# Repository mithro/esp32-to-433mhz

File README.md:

# esp32-to-433mhz

> [!CAUTION]
> **AI in use, use at own risk.**

A small carrier board that turns an **ESP32-C3 SuperMini** and a cheap
**433 MHz radio board** into one 29&nbsp;x&nbsp;38 mm unit. It takes any of three
common 2x4-header radios in the same socket:

* the blue **Ebyte E07-M1101D** (CC1101, SMA jack),
* the green **D-Sun CC1101** board (same signals, different header order),
* the blue **SX1278 LoRa 433MHz v4.0** breakout (Ai-Thinker Ra-02, IPEX
  antenna).

Same ESP32 pins for every radio, one firmware pin map per board, and every
track on one copper layer so it can even be etched at home.

| With the E07-M1101D (CC1101) | With the Ra-02 breakout (SX1278) |
| --- | --- |
|  |  |

The KiCad 9 project is `hardware/esp32c3-radio-adapter`. Ready-to-upload
Gerber packages are attached to the
[latest release](https://github.com/mithro/esp32-to-433mhz/releases/latest).

Contents:

* [What you need](#what-you-need)
* [Getting the board made](#getting-the-board-made)
* [Assembling it](#assembling-it)
* [Pin map for firmware](#pin-map-for-firmware)
* [Jumper-wire version (no adapter needed)](#jumper-wire-version-no-adapter-needed)
* [Further reading](#further-reading)

## What you need

Everything is a stock AliExpress / eBay / Amazon part costing a few
dollars. The "Buy" links are AliExpress searches for the listing names;
the "Details" links go to that board's page in this repository, with its
dimensions, pinout and sources.

### Boards

| Board | Buy | How to recognise it | Details |
| --- | --- | --- | --- |
| **ESP32-C3 SuperMini** | [ESP32-C3 SuperMini](https://www.aliexpress.com/w/wholesale-esp32-c3-supermini.html) | 18&nbsp;x&nbsp;22.5 mm, USB-C, 8 castellated pins per side, ceramic antenna at the far end from the USB-C. Usually ships with two 1x8 pin headers. | [dimensions and pinout](hardware/parts/esp32-c3-supermini/) |
| **One radio board**, any of: | | | |
| Ebyte E07-M1101D-SMA (CC1101) | [E07-M1101D](https://www.aliexpress.com/w/wholesale-e07-m1101d.html), also sold as "TENSTAR CC1101 433MHz wireless module" | Blue, 15&nbsp;x&nbsp;30 mm, 2x4 header at one end, SMA jack at the other, PCB marked "E07-M1101D V2.0". Take the -SMA, not the -TH spring-antenna variant that search leads with. Needs a 433 MHz SMA antenna (often included). | [Ebyte product page](https://www.cdebyte.com/products/E07-M1101D-SMA), [part page](hardware/parts/cc1101-e07-m1101d/) |
| D-Sun CC1101 (green) | [CC1101 433MHz module](https://www.aliexpress.com/w/wholesale-cc1101-433mhz-module.html), pick the green one | Green, 14.4&nbsp;x&nbsp;30 mm, silk "433MHz D-Sun CC1101", 2x4 header, SMA jack. Needs a 433 MHz SMA antenna. | [part page](hardware/parts/cc1101-dsun/) |
| SX1278 Ra-02 breakout | [SX1278 LoRa 433MHz Ra-02](https://www.aliexpress.com/w/wholesale-sx1278-lora-433mhz-ra-02.html) | Blue 17.5&nbsp;x&nbsp;22.5 mm carrier with the Ai-Thinker Ra-02 can on top, 2x4 header underneath, silk "SX1278 LoRa 433MHz v4.0". Needs a [U.FL (IPEX) to SMA pigtail](https://www.aliexpress.com/w/wholesale-ipex-to-sma-pigtail.html) plus a 433 MHz SMA antenna. | [Ai-Thinker Ra-02 page](https://docs.ai-thinker.com/en/Ra-02/index.html), [part page](hardware/parts/sx1278-ra02-breakout/) |

Get a [433 MHz SMA antenna](https://www.aliexpress.com/w/wholesale-433mhz-sma-antenna.html),
not the 868/915 MHz one many listings bundle with the same radio.

### Headers and small parts

| Ref | Part | Qty | Notes |
| --- | --- | --- | --- |
| J1, J2 | 1x8 male pin header, 2.54 mm | 2 | For the SuperMini; usually in the bag with it. Or solder the SuperMini flat by its castellations and skip these. |
| J3 | 2x4 male pin header, 2.54 mm | 1 | The radio board's own header solders straight into the adapter. Fit a 2x4 female header instead if you want the radio removable. |
| [J4](docs/design-notes.md#expansion-header-j4) | 1x7 male pin header, 2.54 mm | 1 | Expansion header: 3V3 and the spare GPIOs. Optional. |
| [J5](docs/design-notes.md#the-dio2-fly-wire-header) | 1x2 male pin header, 2.54 mm | 1 | DIO2 fly-wire header. Only needed for raw OOK on the SX1278. |
| [JP1](docs/design-notes.md#radio-type-strap-jp1-r1) | 1x2 male pin header + jumper cap, 2.54 mm | 1 | Radio-type strap. Jumper fitted for the Ra-02, open for a CC1101. |
| R1 | 0805 0 ohm resistor | 0 or 1 | Permanent alternative to the JP1 jumper (Ra-02 only). |
| R2, R3, R4 | 0805 4.7 kOhm resistors | 0 | Do-not-populate pull-ups on the boot straps: GPIO8 and GPIO2 (on J4) and GPIO9 (unused). Only if something you add holds one of them low at boot. |
| | M2 screws or standoffs | 4 | The corner holes are 2.2 mm. |
| | Thin insulated wire, 30 to 50 mm | 1 | The DIO2 fly wire (Ra-02 only): a strand of wire-wrap or enamelled wire. |

A strip of 40-pin "breakaway" male header covers J1, J2, J4, J5 and JP1.

## Getting the board made

1. Download `esp32c3-radio-adapter-<version>-jlcpcb.zip` or
   `...-nextpcb.zip` from the
   [latest release](https://github.com/mithro/esp32-to-433mhz/releases/latest).
   Each zip is a complete Gerber + drill package for that fab, with a
   `README.txt` of the ordering options.
2. Upload the zip to [JLCPCB](https://jlcpcb.com) or
   [NextPCB](https://www.nextpcb.com) as a new PCB order.
3. Order with these options (all fab defaults, no special processes):

| Option | Value |
| --- | --- |
| Size | 29.0&nbsp;x&nbsp;38.0 mm |
| Layers | 2 |
| Thickness | 1.6 mm FR-4 |
| Copper | 1 oz |
| Finish | ENIG preferred, HASL fine |
| Solder mask / silk | any colour, silkscreen both sides |
| Castellated holes | not needed |

The packages are rebuilt by CI on every push to `main` and carry the
`git describe` version in their name; the same string is printed in the
board's title block.

**Etching it yourself.** Every track is on the bottom copper; the top has
only pads and a ground pour. So the bottom layer alone works as a
single-sided board, with two limits: the SuperMini must go on with pin
headers (laid flat it would sit on the copper side, where its pin rows
come out mirrored), and R1 sits on the copper side. Use the `.GBL`,
`.GBO` and `.DRL` files from the package.

## Assembling it

1. **Radio-type strap first.** For the Ra-02 breakout, fit JP1 and put a
   jumper on it (or solder a 0 ohm resistor in R1 on the bottom). For
   either CC1101 board, leave JP1 empty or open.
2. **SuperMini.** It lies on its side along the left edge, USB-C hanging
   off the board; the silk shows the outline and pin names. Either solder
   its two 1x8 headers through the 1.0 mm holes (long pins down through
   the adapter, the plastic body between the two boards), or lay it flat
   on the top side and solder the castellations to the extended pads.
3. **J4, J5.** Optional; solder them from the top so the pins stand up.
   The silk under J4 names the pins the way the SuperMini does; J5's pins
   are "21" and "20 DIO2".
4. **Radio board.** It plugs in component side up, hanging off the bottom
   edge with its antenna connector pointing away from the adapter. Pin 1
   (GND) is the square pad at the right of the outer row. Solder its
   header pins into the 2x4 holes, or into a female socket fitted there.
5. **DIO2 fly wire (Ra-02, raw OOK only).** Run a wire from the
   breakout's DIO2 land to J5 pin 2 (GPIO20). DIO2 is not on the 2x4
   header: it is the Ra-02 module's pin 7, whose land sticks 0.8 mm out
   past the module's edge on the right-hand side, about 9 mm down from the
   header edge. The pinout diagram below marks it, and
   [Adding the DIO2 wire](hardware/parts/sx1278-ra02-breakout/dio2-wire.md)
   shows the radio end and how to check it landed.
6. **Antenna.** Screw it on the E07 or D-Sun's SMA jack; for the Ra-02,
   clip the pigtail's U.FL plug onto the module and screw the antenna on
   the pigtail. The DIO2 wire and the pigtail both want strain relief:
   a dab of hot glue over the wire's solder joint is enough.

| Top | Bottom (all the tracks) |
| --- | --- |
|  |  |

The silkscreen outlines the two mechanical keep-outs, the footprints of the
SuperMini and of the plugged-in radio board. J5 sits in the band between
them and is the only thing that fits there.

## Pin map for firmware

The socket's eight positions go to fixed GPIOs. Which signal each carries
depends on the radio, so firmware needs one pin map per board:

| Socket position | ESP32-C3 GPIO | E07-M1101D (blue CC1101) | D-Sun (green CC1101) | Ra-02 breakout (SX1278) |
| --- | --- | --- | --- | --- |
| 1 | GND | GND | GND | GND |
| 2 | 3V3 | VCC | VCC | 3V3 |
| 3 | GPIO10 | GDO0 (radio out) | MOSI | RST (radio in) |
| 4 | GPIO1 | CSN | SCK | NSS |
| 5 | GPIO3 | SCK | MISO (radio out) | SCK |
| 6 | GPIO4 | MOSI | GDO2 (radio out) | MOSI |
| 7 | GPIO7 | MISO (radio out) | GDO0 (radio out) | MISO (radio out) |
| 8 | GPIO6 | GDO2 (radio out) | CSN | DIO0 (radio out) |
| J5 pin 2 | GPIO20 | | | DIO2/DATA (fly wire) |
| JP1 / R1 | GPIO5 | open | open | strapped to GND |

The same maps, signal first:

| Signal | E07-M1101D | D-Sun | Ra-02 |
| --- | --- | --- | --- |
| MOSI | GPIO4 | GPIO10 | GPIO4 |
| MISO | GPIO7 | GPIO3 | GPIO7 |
| SCK | GPIO3 | GPIO1 | GPIO3 |
| CSN / NSS | GPIO1 | GPIO6 | GPIO1 |
| GDO0 / DIO0 | GPIO10 | GPIO7 | GPIO6 |
| GDO2 | GPIO6 | GPIO4 | |
| RST | | | GPIO10 |
| DIO2/DATA | | | GPIO20 |

**Telling the boards apart.** GPIO5 is the radio-type strap. Read it with
the internal pull-up enabled: low means the Ra-02 (jumper fitted), high
means a CC1101 board. The three-state read that also covers the SX1278
module adapter is in the
[design notes](docs/design-notes.md#radio-type-strap-jp1-r1). The two
CC1101 boards are told apart without driving anything: an unconfigured CC1101 clocks about 135 kHz out of GDO0, so
whichever of GPIO10 (blue board) and GPIO7 (green board) is toggling at
power-up names the board. In the jumper-wire build the strap goes to GPIO0
instead of GND, so drive GPIO0 low as an output before reading GPIO5.

**Why DIO2 matters on the SX1278.** In its continuous mode the raw
demodulated bitstream is available only on the DIO2/DATA pin. Packet mode
carries only what the packet handler can frame, which suits Fineoffset
weather stations but not the OOK remotes this node exists to hear and key.
The Ra-02 breakout leaves DIO2 unconnected, hence the fly wire to GPIO20.

**Never put a radio pin on GPIO2, GPIO8 or GPIO9.** They are ESP32-C3 boot
straps; a radio pin's capacitance makes the strap rise too slowly at reset
and the chip drops into USB download mode instead of running. This was
measured on the bench and later confirmed over JTAG -- on an affected board
the GPIO_STRAP_REG latch reads the download pattern even though the live
GPIO9 reads high -- and is not fixable in software, which is why the socket
uses GPIO1 rather than GPIO9.

## Jumper-wire version (no adapter needed)

The same hook-up with Dupont jumper wires, so the firmware pin map is
identical and you can test everything before ordering boards. Plug the
female-to-female wires onto the SuperMini's headers and the radio board's
2x4 header. Both boards are drawn from the back, pins towards you.

| Wire | SuperMini pin | E07-M1101D | D-Sun | Ra-02 |
| --- | --- | --- | --- | --- |
| brown | G | GND | GND | GND |
| red | 3V3 | VCC | VCC | 3V3 |
| grey | GPIO10 | GDO0 | MOSI | RST |
| purple | GPIO1 | CSN | SCK | NSS |
| blue | GPIO3 | SCK | MISO | SCK |
| white | GPIO4 | MOSI | GDO2 | MOSI |
| green | GPIO7 | MISO | GDO0 | MISO |
| yellow | GPIO6 | GDO2 | CSN | DIO0 |
| orange | GPIO5 | not fitted | not fitted | to the SuperMini's GPIO0 (radio-type strap) |
| black | GPIO20 | | | DIO2, soldered to the module's pin-7 land |

The Ra-02's orange strap wire goes to GPIO0 rather than GND because the
SuperMini's only GND pin is taken by the brown wire; the firmware drives
GPIO0 low while it reads the strap. The black DIO2 wire has no header pin
at the radio end: solder it to the module's pin-7 castellation or the land
just outside it, on the face away from the header pins. The header
pinouts, with the DIO2 land marked on both faces:

## Printing a case

A two-part case that fits the adapter with either radio is in
`hardware/case/` as STL files. Every
[release](https://github.com/mithro/esp32-to-433mhz/releases/latest)
carries it as `esp32c3-radio-adapter-case-<version>.zip`, plus the two
`.stl` files loose for dropping straight into a slicer. The zip holds the
STL files in print orientation, the case's STEP models, and a README.txt
with the parts' sizes, home FDM print settings and how to order them from
JLCPCB's 3D-printing service.
In the pictures and the notes below, the **front** is the antenna end,
the **back** the SuperMini end with the pry notch on the seam, and the
**left** wall the one with the USB-C window. The top half is the darker
shade.

Closed, with the E07-M1101D inside (its SMA jack through the front wall):

Open, the adapter pressed onto the pegs in the bottom half, with the Ra-02
breakout and its U.FL-to-SMA pigtail in the socket (the drawn pigtail runs
straight to the bulkhead; a real one is longer, with the excess lying
beside the breakout):

The halves on their own, and the slotted top:

| Bottom half: pegs, lip and the four snap tabs | Top half from below: bosses, grooved skirt, USB-C window, antenna hole | The slotted top half closed over the E07 |
| --- | --- | --- |
|  |  |  |

The same views with the other radio (the Ra-02 closed, the E07-M1101D
open) and the exploded views are in
[3D models and case design](docs/3d-models.md#the-printed-case).

* Two halves that snap together: `esp32c3-radio-adapter-case-bottom.stl`
  and `esp32c3-radio-adapter-case-top.stl`, each printed open side up. No
  supports, no screws; 2.2 mm walls; 36.2&nbsp;x&nbsp;66.7&nbsp;x&nbsp;16.7 mm
  outside. Trim every pin under the board to about 1 mm first: the floor
  counts on it.
* The board presses onto four 2.15 mm pegs in the bottom half (they fit
  the 2.2 mm M2 corner holes), and bosses in the top half hold it there
  once the case is shut. The SuperMini can be on its headers or soldered
  flat by its castellations.
* The seam runs through the connectors: the antenna hole and the USB-C
  window are half in each half, so the connectors lie in the bottom half's
  cut-outs and the top closes over them. One 6.6 mm hole in the front wall
  serves both radios: the E07-M1101D's SMA jack pokes through it, and the
  Ra-02's U.FL-to-SMA pigtail bulkhead is clamped in it by its nut, with
  the spare cable stowed beside the breakout.
* Four snap tabs on the bottom half click into grooves in the top half's
  skirt; the notch at the seam on the back takes a fingernail to open it.
  It is not water-tight and does not try to be.
* `esp32c3-radio-adapter-case-top-slot.stl` is the same top half with a
  slot over the spare-GPIO header J4, for jumper wires out of the closed
  case; print it instead of the plain top if you want that.
* The package's README.txt has the print settings, what to inspect (the
  0.8 mm snap tabs, the peg fit, which depends on the printer's
  calibration) and the material to pick at a service.

The case is generated from the same dimensions as the boards by
`scripts/build_case.py`; see [3D models and case design](docs/3d-models.md#the-printed-case).
Dimensioned drawings of both halves, with a checklist of caliper
measurements for a printed part, are in [Case drawings](docs/case-drawings.md).

## Further reading

* [Design notes](docs/design-notes.md): why the GPIOs are what they are,
  how everything routes on one layer, the expansion header J4, the DIO2
  header J5, the mechanical keep-outs and the radio-type strap.
* [Component boards](hardware/parts/): a page per board -- the SuperMini
  and each radio -- with its dimensions, pinout, where to buy it and the
  KiCad reproduction its footprints were checked against.
* [3D models and case design](docs/3d-models.md): STEP/GLB assemblies on
  every release, the dimensions a case needs, and the printed case.
* [SX1278 castellated module adapter](docs/sx1278-module-adapter.md): a
  second, two-layer carrier for the solder-down 16-pin SX1278 module,
  `hardware/esp32c3-sx1278-adapter`.
* [Development](docs/development.md): regenerating the KiCad projects
  from the scripts, running ERC/DRC, and how CI builds the release
  packages.

Not part of this repository, but worth a look before writing firmware from
scratch:
[OpenMQTTGateway's RF gateway](https://docs.openmqttgateway.com/use/rf.html#what-is-an-rf-gateway)
is ESP32 firmware that bridges 433&nbsp;MHz to MQTT and already supports both
radio families this adapter takes: CC1101 boards and SX127x modules. It
offers four receiver flavours -- RCSwitch, Pilight and RF2 receive and
transmit, RTL_433 receives only but knows the most devices. Its documented
ESP32 + CC1101 builds are named as whole boards (Heltec WiFi LoRa 32,
LilyGo LoRa 32, ESP32 DOIT DevKit, Ai-Thinker R01) rather than as a pin
map, so this adapter's GPIOs would have to be mapped onto it, and the
SX1278's DIO2 fly wire has no obvious counterpart there. **Nothing here has
been tried against it yet** -- this is a lead to follow, not a tested route.

## Licence

Apache License 2.0, see `LICENSE`.

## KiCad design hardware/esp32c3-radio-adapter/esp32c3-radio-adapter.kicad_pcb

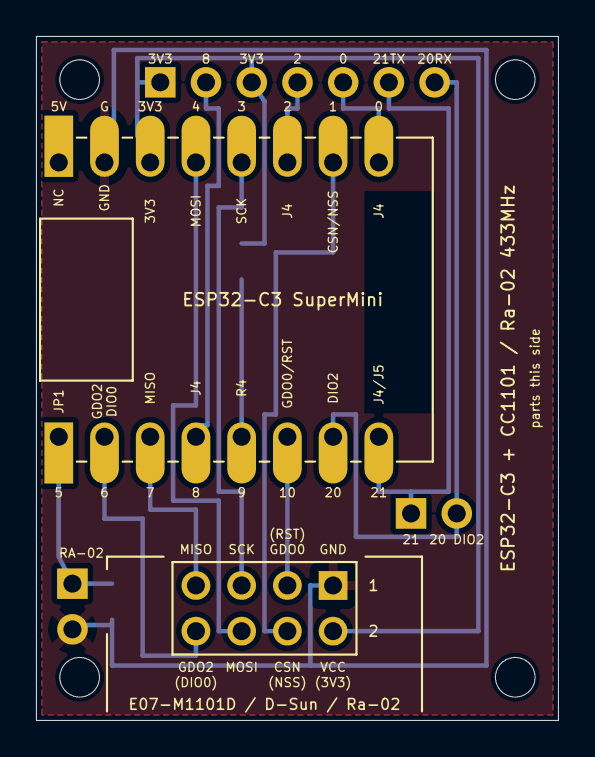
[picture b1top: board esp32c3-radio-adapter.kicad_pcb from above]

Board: 2 copper layers, 29.0 x 38.0 mm, 14 parts (0 on the bottom side), 15 nets.

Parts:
H1, H2, H3, H4: MountingHole; MountingHole_2.2mm_M2
J1: Conn_01x08; SuperMini_Row_1x08_P2.54mm_THT_Castellated_Down
J2: Conn_01x08; SuperMini_Row_1x08_P2.54mm_THT_Castellated_Up
J3: E07-M1101D_or_Ra-02; PinSocket_2x04_P2.54mm_E07
J4: Expansion; PinHeader_1x07_P2.54mm_Vertical
J5: DIO2/DATA; PinHeader_1x02_P2.54mm_Vertical
JP1: RA-02; PinHeader_1x02_P2.54mm_Vertical_AlongY
R1: 0R; R_0805_2012Metric_HandSolder_AlongY_Back
R2, R3: 4k7; R_0805_HeaderPullup
R4: 4k7; R_0805_2012Metric_HandSolder_AlongY_Back

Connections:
+3V3: J2.3, J3.2, J4.1, J4.3, R2.1, R3.1, R4.1
CSN_NSS: J2.7, J3.4
GDO0_RST: J1.6, J3.3
GDO2_DIO0: J1.2, J3.8
GND: J2.2, J3.1, JP1.2, R1.2
GPIO0: J2.8, J4.5
GPIO2: J2.6, J4.4, R3.2
GPIO8: J1.4, J4.2, R2.2
GPIO9: J1.5, R4.2
GPIO20: J1.7, J4.7, J5.2
GPIO21: J1.8, J4.6, J5.1
MISO: J1.3, J3.7
MOSI: J2.4, J3.6
RADIO_ID: J1.1, JP1.1, R1.1
SCK: J2.5, J3.5

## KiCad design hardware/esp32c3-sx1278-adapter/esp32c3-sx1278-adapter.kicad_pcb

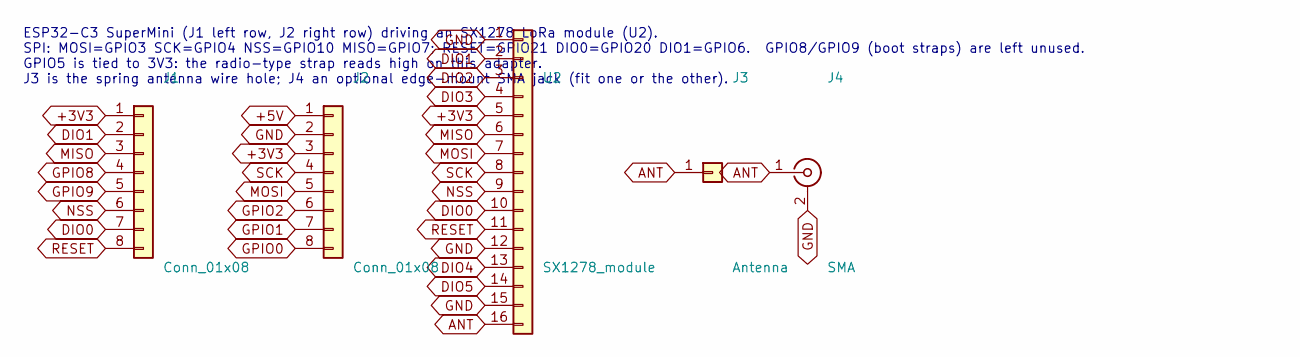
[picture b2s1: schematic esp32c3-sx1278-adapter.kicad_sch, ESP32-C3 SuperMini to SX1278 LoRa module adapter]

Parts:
J1, J2: Conn_01x08; SuperMini_Header_1x08_P2.54mm_THT
J3: Antenna; Antenna_Wire_Hole_1.0mm
J4: SMA; SMA_EdgeMount_E07
U2: SX1278_module; SX1278_Module_16pin_Land

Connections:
+3V3: J1.1, J2.3, U2.5
+5V: J2.1
ANT: J3.1, J4.1, U2.16
DIO0: J1.7, U2.10
DIO1: J1.2, U2.2
DIO2: U2.3
DIO3: U2.4
DIO4: U2.13
DIO5: U2.14
GND: J2.2, J4.2, U2.1, U2.12, U2.15
GPIO0: J2.8
GPIO1: J2.7
GPIO2: J2.6
GPIO8: J1.4
GPIO9: J1.5
MISO: J1.3, U2.6
MOSI: J2.5, U2.7
NSS: J1.6, U2.9
RESET: J1.8, U2.11
SCK: J2.4, U2.8

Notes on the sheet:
ESP32-C3 SuperMini (J1 left row, J2 right row) driving an SX1278 LoRa module (U2). SPI: MOSI=GPIO3 SCK=GPIO4 NSS=GPIO10 MISO=GPIO7; RESET=GPIO21 DIO0=GPIO20 DIO1=GPIO6. GPIO8/GPIO9 (boot straps) are left unused. GPIO5 is tied to 3V3: the radio-type strap reads high on this adapter. J3 is the spring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

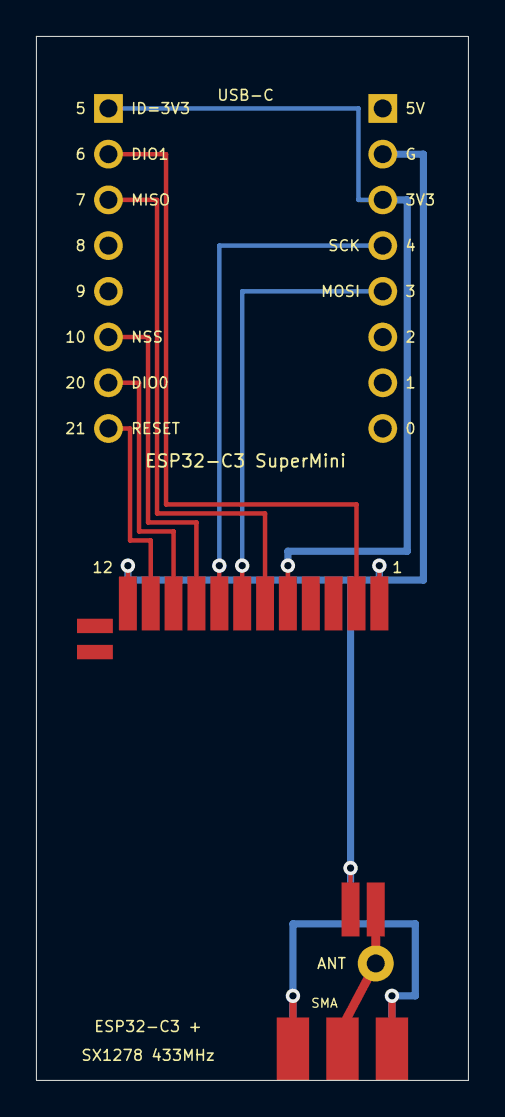
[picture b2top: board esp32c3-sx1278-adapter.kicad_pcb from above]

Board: 2 copper layers, 24.0 x 58.0 mm, 5 parts (0 on the bottom side), 10 nets.

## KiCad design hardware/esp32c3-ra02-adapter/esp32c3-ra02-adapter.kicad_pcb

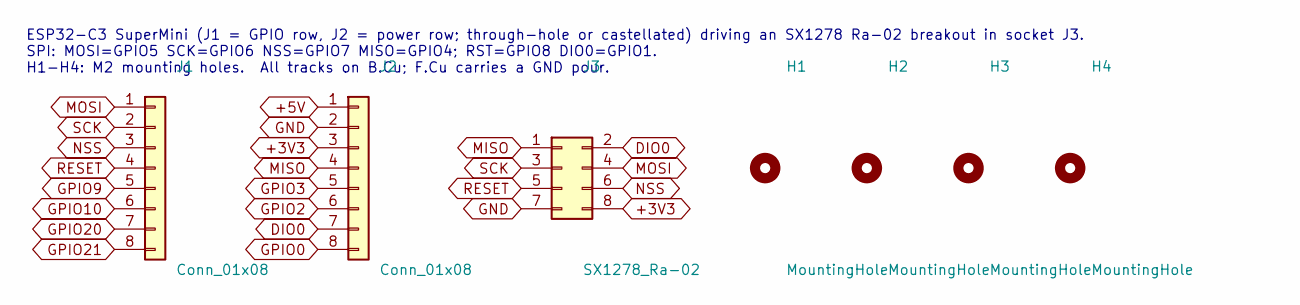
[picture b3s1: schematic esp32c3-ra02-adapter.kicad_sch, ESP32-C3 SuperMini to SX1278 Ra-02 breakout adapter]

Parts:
H1, H2, H3, H4: MountingHole; MountingHole_2.2mm_M2
J1: Conn_01x08; SuperMini_Row_1x08_P2.54mm_THT_Castellated_Down
J2: Conn_01x08; SuperMini_Row_1x08_P2.54mm_THT_Castellated_Up
J3: SX1278_Ra-02; PinSocket_2x04_P2.54mm_Ra02_Breakout

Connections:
+3V3: J2.3, J3.8
+5V: J2.1
DIO0: J2.7, J3.2
GND: J2.2, J3.7
GPIO0: J2.8
GPIO2: J2.6
GPIO3: J2.5
GPIO9: J1.5
GPIO10: J1.6
GPIO20: J1.7
GPIO21: J1.8
MISO: J2.4, J3.1
MOSI: J1.1, J3.4
NSS: J1.3, J3.6
RESET: J1.4, J3.5
SCK: J1.2, J3.3

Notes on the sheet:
ESP32-C3 SuperMini (J1 = GPIO row, J2 = power row; through-hole or castellated) driving an SX1278 Ra-02 breakout in socket J3. SPI: MOSI=GPIO5 SCK=GPIO6 NSS=GPIO7 MISO=GPIO4; RST=GPIO8 DIO0=GPIO1. H1-H4: M2 mounting holes. All tracks on B.Cu; F.Cu carries a GND pour.

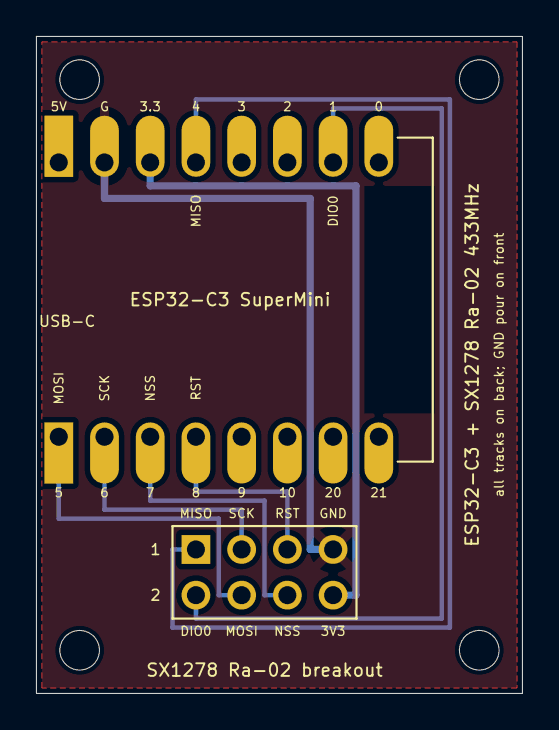
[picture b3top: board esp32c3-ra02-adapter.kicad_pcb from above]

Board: 2 copper layers, 27.0 x 36.5 mm, 7 parts (0 on the bottom side), 8 nets.

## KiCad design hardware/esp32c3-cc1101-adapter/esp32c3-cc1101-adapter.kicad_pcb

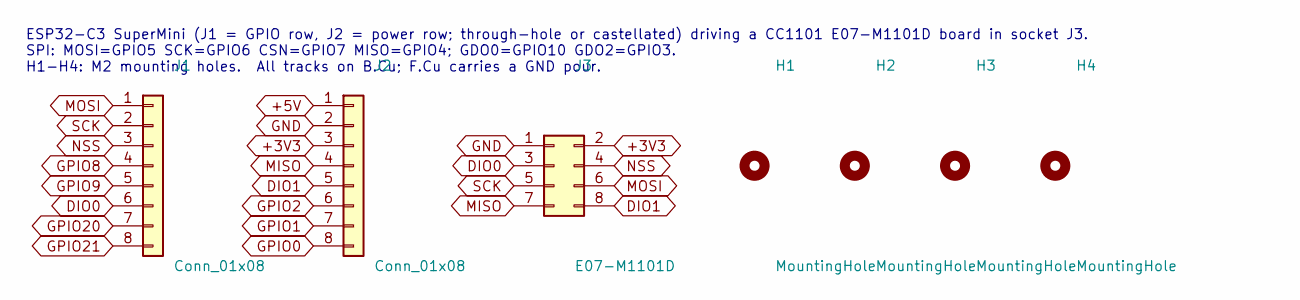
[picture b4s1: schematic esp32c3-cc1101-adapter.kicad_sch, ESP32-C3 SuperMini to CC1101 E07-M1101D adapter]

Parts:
H1, H2, H3, H4: MountingHole; MountingHole_2.2mm_M2
J1: Conn_01x08; SuperMini_Row_1x08_P2.54mm_THT_Castellated_Down
J2: Conn_01x08; SuperMini_Row_1x08_P2.54mm_THT_Castellated_Up
J3: E07-M1101D; PinSocket_2x04_P2.54mm_E07

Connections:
+3V3: J2.3, J3.2
+5V: J2.1
DIO0: J1.6, J3.3
DIO1: J2.5, J3.8
GND: J2.2, J3.1
GPIO0: J2.8
GPIO1: J2.7
GPIO2: J2.6
GPIO8: J1.4
GPIO9: J1.5
GPIO20: J1.7
GPIO21: J1.8
MISO: J2.4, J3.7
MOSI: J1.1, J3.6
NSS: J1.3, J3.4
SCK: J1.2, J3.5

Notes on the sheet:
ESP32-C3 SuperMini (J1 = GPIO row, J2 = power row; through-hole or castellated) driving a CC1101 E07-M1101D board in socket J3. SPI: MOSI=GPIO5 SCK=GPIO6 CSN=GPIO7 MISO=GPIO4; GDO0=GPIO10 GDO2=GPIO3. H1-H4: M2 mounting holes. All tracks on B.Cu; F.Cu carries a GND pour.

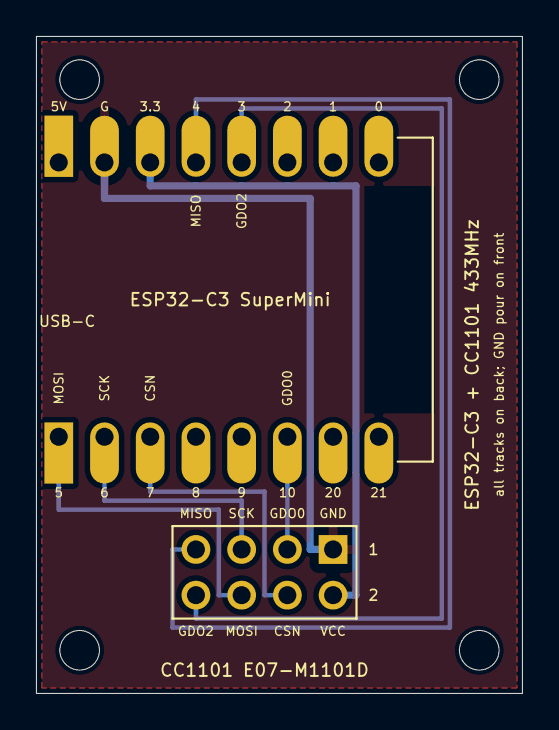
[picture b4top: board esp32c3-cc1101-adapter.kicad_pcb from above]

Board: 2 copper layers, 27.0 x 36.5 mm, 7 parts (0 on the bottom side), 8 nets.

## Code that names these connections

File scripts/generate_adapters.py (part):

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swaps MOSI and SCK) so firmware needs only a pin map per radio.  Routing is
done by hand in this file and checked by DRC (scripts/verify_boards.py).

GPIO choice: GPIO2/8/9 are ESP32-C3 boot strapping pins, so no socket
position that is a radio output on any board goes to them; they carry only
ESP32 outputs (RESET) or a position that is an input on every radio (the
chip select).  GPIO20/21 (UART) carry no socket position; on the socket
adapter they also reach J5, the fly-wire header beside the socket, where
GPIO20 is the SX1278's DIO2/DATA pin.
"""

from __future__ import annotations
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# SX1278 module adapter's assignment (see RADIO_PINMAP for the socket
# adapter's, which it matches apart from swapping MOSI and SCK).
PINMAP = {
    "DIO1": "GPIO6",  # GDO2 on the CC1101
    "MISO": "GPIO7",
    "NSS": "GPIO10",  # CSN on the CC1101; moved off the GPIO9 boot strap
    "DIO0": "GPIO20",  # GDO0 on the CC1101; moved off GPIO10 to make room for NSS
    "RESET": "GPIO21",  # SX1278 module only; moved off the GPIO8 boot strap
    "MOSI": "GPIO3",  # (GPIO4 on the socket adapter: the two swap so this adapter's bottom copper routes)
    "SCK": "GPIO4",
    "+3V3": "GPIO5",  # radio-type strap (see RADIO_ID below): tied high on this adapter
}

SM_PITCH = 2.54
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SM_RIGHT_X = SM_LEFT_X + 15.24  # 19.24
SM_PIN1_Y = 4.0
SM_BODY = (SM_LEFT_X - 1.38, SM_PIN1_Y - 1.74, SM_RIGHT_X + 1.38, SM_PIN1_Y - 1.74 + 22.52)  # 2.62,2.26 .. 20.62,24.78
SM_LEFT_GPIO = ["GPIO5", "GPIO6", "GPIO7", "GPIO8", "GPIO9", "GPIO10", "GPIO20", "GPIO21"]
SM_RIGHT_GPIO = ["+5V", "GND", "+3V3", "GPIO4", "GPIO3", "GPIO2", "GPIO1", "GPIO0"]
SM_LEFT_SILK = ["5", "6", "7", "8", "9", "10", "20", "21"]  # as printed on the SuperMini
SM_RIGHT_SILK = ["5V", "G", "3V3", "4", "3", "2", "1", "0"]
SM_PAD = 1.6
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CONN2 = SymbolRef("Connector_Generic.kicad_sym", "Connector_Generic", "Conn_01x02")
RES = SymbolRef("Device.kicad_sym", "Device", "R")

# Radio-type strap: firmware reads GPIO5 (net RADIO_ID) once with the internal
# pull-down and once with the pull-up enabled, which tells the three states
# apart.  GPIO5 is not an ESP32-C3 boot strapping pin, so tying it is safe.
RADIO_ID_GPIO = "GPIO5"
RADIO_ID_STATES = {
    "floating": "CC1101 E07-M1101D in the socket adapter (no jumper on JP1, R1 not fitted)",
    "low": "SX1278 Ra-02 breakout in the socket adapter (jumper on JP1 or 0R in R1, both to GND)",
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SX_H = 58.0
SMA_X = 17.0  # optional edge-mount SMA jack on the bottom edge (ground legs at +/-4.25)

SX_PINS = ["GND", "DIO1", "DIO2", "DIO3", "+3V3", "MISO", "MOSI", "SCK", "NSS", "DIO0", "RESET", "GND", "DIO4", "DIO5", "GND", "ANT"]


def row_x(pin: int) -> float:
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    ]
    return Footprint(
        name="SX1278_Module_16pin_Land",
        descr="Land pattern for the 16-pin castellated PXL1276-D01 style SX1278 module, rotated so the 12-pad row is along the top edge (pin 1 at the right) and ANT/GND on the bottom edge; pads extend 1.5 mm outside the module edge for soldering",
        tags="SX1278 LoRa module land pattern castellated",
        pads=pads,
        extra=extra,
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    )
    bx, by = d.bx, d.by
    left, right = supermini_nets(PINMAP)
    supermini_parts(d, left, right, labels={RADIO_ID_GPIO: "ID=3V3"})
    # The module model is drawn with its 12-pad edge on the left (as the reference board
    # under hardware/parts/); here it is turned 90 degrees clockwise so that edge is on top.
    d.parts.append(Part("U2", sx1278_land_fp(), (bx + MOD_L, by + MOD_T), CONN16, "SX1278_module", {str(i + 1): n for i, n in enumerate(SX_PINS)}, (127.0, 101.6), "SX1278 LoRa module",
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    # outer bus and the outer lane, and the GPIO order matches the module's
    # pad order (DIO1 17.78 > MISO 12.7 > NSS 8.89 > DIO0 7.62), so drops
    # never cross another lane.  (Pin 4, RESET, is on B.Cu.)
    left_bus(2, 7.2, 26.0, row_x(2), "DIO1")  # GPIO6 -> DIO1 pad 2
    left_bus(3, 6.7, 26.5, row_x(6), "MISO")  # GPIO7 -> MISO pad 6
    left_bus(6, 6.2, 27.0, row_x(9), "NSS")  # GPIO10 -> NSS pad 9
    left_bus(7, 5.7, 27.5, row_x(10), "DIO0")  # GPIO20 -> DIO0 pad 10
    left_bus(8, 5.2, 28.0, row_x(11), "RESET")  # GPIO21 -> RESET pad 11

    # B.Cu: power, reset and NSS (from the right column), with vias just
    # above the land pads.
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    T.append(Track("GND", B, 0.4, [(bx + gnd_bot_x, by + GND_TRUNK_Y), (bx + gnd_bot_x, by + MOD_B - 2.3)]))
    V.append(Via("GND", (bx + gnd_bot_x, by + MOD_B - 2.3)))
    T.append(Track("GND", F, TRACK, [(bx + gnd_bot_x, by + MOD_B - 2.3), (bx + gnd_bot_x, by + MOD_B + 0.5)]))
    # Antenna: module ANT pad -> wire hole -> centre pin of the optional SMA.
    T.append(Track("ANT", F, 0.5, [(bx + MOD_R - 1.4, by + MOD_B + 0.5), (bx + MOD_R - 1.4, by + ANT_HOLE_Y), (bx + SMA_X, by + SX_H - SMA_PAD_L + 0.5), (bx + SMA_X, by + SX_H - SMA_PAD_L / 2)]))
    # SMA ground legs, on B.Cu from the via feeding the module's bottom GND pad.
    leg_y = SX_H - SMA_PAD_L / 2
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# Socket-adapter geometry (mm).  Everything below is routed on B.Cu alone.
SOCKET_Y = 30.5  # socket outer row; inner row 2.54 below
LANES = [CC_BOT_Y + 3.05 + i * 0.5 for i in range(4)]  # 25.29 .. 26.79: lanes under the GPIO row's keyhole copper (to 24.84)
LANE_A = LANES[0]  # GPIO21's lane, above J5's pads; GPIO20 takes J5_LANE, below them
UNDER_Y = 34.95  # GND lane under the socket (pads reach 33.84), clear of the bottom holes
GDO2_X, GDO2_Y = 5.9, 34.4  # GDO2/DIO0 goes down the left of the socket and enters its pad from below
TOP_GND_Y, TOP_3V3_Y = 0.75, 1.2  # GND and 3V3 lanes along the top edge, above the expansion header
GND_RISE_X, V33_RISE_X = 4.3, 5.6  # where they leave the power row, between the top-left hole and header pin 1
STRIP = {"GPIO21": 22.9, "GPIO20": 23.35, "+3V3": 24.55, "GND": 25.0}  # lanes down the strip right of the SuperMini
MID_A, MID_B = CC_BOT_Y - 1.74, CC_BOT_Y - 1.24  # 20.5 / 21.0: jogs between the rows, just above the GPIO row's rings (21.44)
GPIO8_RISE_X = 9.5  # GPIO8 climbs between the GPIO3 and GPIO4 drops to reach the header
# GPIO9's pull-up R4 sits on the back between the rows, above GPIO9's pad.
# GPIO9 is boxed in on the back copper: SCK's drop passes left of its pad
# and CSN's right of it, and SCK has to enter socket pin 5 from directly
# below it.  So SCK's drop moves one gap left (to 10.13) as soon as it
# leaves its pad, and 3V3 comes down from J4 pin 3 through the power row's
# gap between GPIO3 and GPIO2 into R4's top pad; R4's bottom pad drops
# straight into GPIO9.  CSN's drop keeps right of R4 until it is above the
# GPIO row's rings, then steps into the gap between GPIO9 and GPIO10.
SCK_JOG_Y = 9.5  # SCK leaves its pad downward and steps left here, above R4
V33_DROP_X = 12.67  # 3V3 for R4: down the power row's gap between GPIO3 (11.4) and GPIO2 (13.94)
R4_X, R4_Y = 11.4, 12.5  # pads at 11.5 (+3V3) and 13.5 (GPIO9), in GPIO9's column
CSN_X = 13.3  # CSN's drop right of R4; it steps to 12.67 at MID_B to pass the GPIO row


# Socket net -> GPIO.  The socket also takes the green D-Sun CC1101 board,
# whose signals sit in a different order, with a different pin map in
# firmware; so NO socket position may be a boot strapping pin (GPIO2/8/9).
# A radio pin on a strap loads it enough that, through the ESP32's weak
# internal pull-up, it rises too slowly for the ROM to read it high at reset:
# the chip straps into USB download mode and never runs the app (measured on
# the bench, 2026-09-06).  Position 4 (CSN_NSS) therefore takes GPIO1; GPIO9
# is left unconnected -- an unconnected strap floats high on the internal
# pull-up, the safest state -- and GPIO8/GPIO2 stay on the header with pull-ups.
RADIO_PINMAP = {"MOSI": "GPIO4", "SCK": "GPIO3", "CSN_NSS": "GPIO1", "GDO0_RST": "GPIO10", "MISO": "GPIO7", "GDO2_DIO0": "GPIO6", "RADIO_ID": RADIO_ID_GPIO}
# Expansion header J4 on the top edge, centred between the mounting holes:
# 3V3 plus every GPIO the radio does not use (5V cannot be reached on one
# layer: the top-left hole sits over its pad).  GPIO2/0 rise straight from
# the power row, GPIO8 climbs from the GPIO row between the rows, and
# GPIO21/20 come from the GPIO row up the right-hand strip.  Each boot
# strap on the header (GPIO8, GPIO2) has a 3V3 pin on its left for its
# pull-up (R2, R3); the second 3V3, pin 3, also feeds R4, the GPIO9 pull-up.
EXP_PINS = ["+3V3", "GPIO8", "+3V3", "GPIO2", "GPIO0", "GPIO21", "GPIO20"]
EXP_UART = {"GPIO21": "TX", "GPIO20": "RX"}  # UART0 on the ESP32-C3
EXP_LABELS = {"+3V3": "3V3", "GPIO8": "8", "GPIO2": "2", "GPIO0": "0", "GPIO21": "21", "GPIO20": "20"}
EXP_Y = 2.55  # header row: pads clear the top lanes above and the jog row below
EXP_X1 = CC_W / 2 - 3 * SM_PITCH  # 6.88: pin 1 of the 7-pin header, so pin 4 is on the board's centre line
EXP_JOG_Y = CC_TOP_Y - 3.0  # 4.0: jogs between the power-row keyhole copper (to 4.4) and the header
# Radio-type strap in the bottom-left corner, left of the plugged-in radio
# board: JP1 (1x2 header, pin 1 = RADIO_ID, pin 2 = GND) with R1 (0805 on
# the back, in parallel) beside it.  RADIO_ID is GPIO5, the first GPIO-row
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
